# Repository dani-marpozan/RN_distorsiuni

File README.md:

# Efectul reactiei negatie asupra distorsiunilor si  semnalelor parazite  

Model 3D

## Schematic

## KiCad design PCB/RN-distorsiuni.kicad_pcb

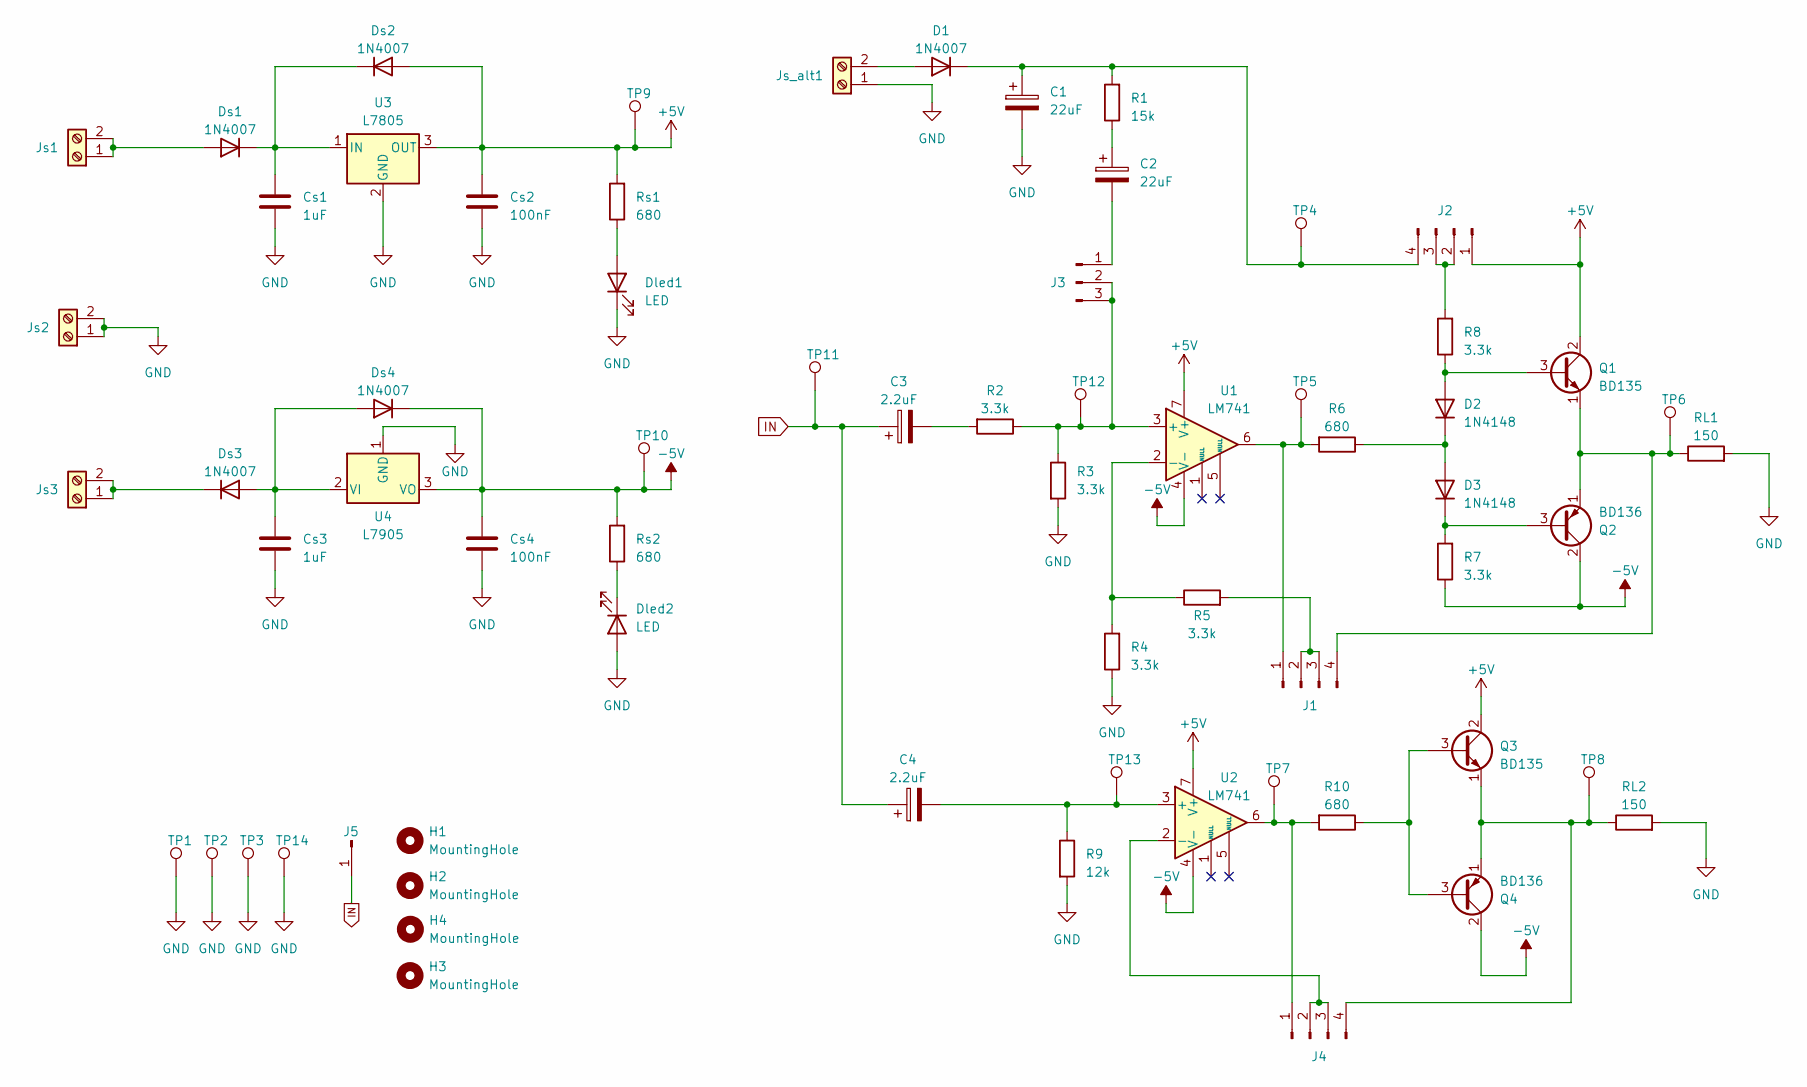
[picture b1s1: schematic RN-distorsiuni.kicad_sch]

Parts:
C1: 22uF; CP_Radial_D6.3mm_P2.50mm
C2: 22uF; C_Radial_D5.0mm_H11.0mm_P2.00mm
C3, C4: 2.2uF; C_Radial_D5.0mm_H11.0mm_P2.00mm
Cs1, Cs3: 1uF; C_Radial_D5.0mm_H11.0mm_P2.00mm
Cs2, Cs4: 100nF; C_Disc_D6.0mm_W2.5mm_P5.00mm
D1: 1N4007; D_DO-41_SOD81_P10.16mm_Horizontal
D2, D3: 1N4148; D_DO-35_SOD27_P7.62mm_Horizontal
Dled1, Dled2: LED; LED_D5.0mm
Ds1, Ds2, Ds3, Ds4: 1N4007; D_DO-41_SOD81_P10.16mm_Horizontal
H1, H2, H3, H4: MountingHole; MountingHole_3.2mm_M3_ISO7380_Pad_TopBottom
J1, J2, J4: Conn_01x04_Pin; PinHeader_1x04_P2.54mm_Vertical
J3: Conn_01x03_Pin; PinHeader_1x03_P2.54mm_Vertical
J5: Conn_01x01_Male; TestPoint
Js1, Js2, Js3: Screw_Terminal_01x02; TerminalBlock_Phoenix_MKDS-1,5-2_1x02_P5.00mm_Horizontal
Js_alt1: Screw_Terminal_01x02; TerminalBlock_Phoenix_MKDS-1,5-2_1x02_P5.00mm_Horizontal
Q1, Q3: BD135; TO-126-3_Vertical
Q2, Q4: BD136; TO-126-3_Vertical
R1: 15k; R_Axial_DIN0207_L6.3mm_D2.5mm_P10.16mm_Horizontal
R2, R3, R4, R5, R7, R8: 3.3k; R_Axial_DIN0207_L6.3mm_D2.5mm_P10.16mm_Horizontal
R6, R10: 680; R_Axial_DIN0207_L6.3mm_D2.5mm_P10.16mm_Horizontal
R9: 12k; R_Axial_DIN0207_L6.3mm_D2.5mm_P10.16mm_Horizontal
RL1, RL2: 150; R_Axial_DIN0207_L6.3mm_D2.5mm_P10.16mm_Horizontal
Rs1, Rs2: 680; R_Axial_DIN0207_L6.3mm_D2.5mm_P10.16mm_Horizontal
TP1, TP2, TP3, TP14: TestPoint
TP4, TP5, TP6, TP7, TP8, TP9, TP10, TP11, TP12, TP13: TestPoint; Kesytone TP Multipurpose 5013
U1, U2: LM741; DIP-8_W7.62mm
U3: L7805; TO-220-3_Vertical
U4: L7905; TO-220-3_Vertical

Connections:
+5V: Cs2.1, Ds2.2 (A), J2.1, Q1.2 (C), Q3.2 (C), Rs1.2, TP9.1, U1.7 (V+), U2.7 (V+), U3.3 (OUT)
-5V: Cs4.1, Ds4.1 (K), Q2.2 (C), Q4.2 (C), R7.1, Rs2.2, TP10.1, U1.4 (V-), U2.4 (V-), U4.3 (VO)
GND: C1.2, Cs1.2, Cs2.2, Cs3.2, Cs4.2, Dled1.1 (K), Dled2.2 (A), Js2.1, Js2.2, Js_alt1.1, R3.2, R4.1, R9.2, RL1.2, RL2.2, TP1.1, TP2.1, TP3.1, TP14.1, U3.2 (GND), U4.1 (GND)
IN: C3.1, C4.1, J5.1, TP11.1
unnamed: C2.1, R1.1
unnamed: C3.2, R2.2
unnamed: D1.2 (A), Js_alt1.2
unnamed: C1.1, D1.1 (K), J2.4, R1.2, TP4.1
unnamed: D2.2 (A), Q1.3 (B), R8.1
unnamed: D2.1 (K), D3.2 (A), R6.1
unnamed: D3.1 (K), Q2.3 (B), R7.2
unnamed: Dled1.2 (A), Rs1.1
unnamed: Dled2.1 (K), Rs2.1
unnamed: Ds1.2 (A), Js1.1, Js1.2
unnamed: Cs1.1, Ds1.1 (K), Ds2.1 (K), U3.1 (IN)
unnamed: Cs3.1, Ds3.2 (A), Ds4.2 (A), U4.2 (VI)
unnamed: Ds3.1 (K), Js3.1, Js3.2
unnamed: J1.1, R6.2, TP5.1, U1.6
unnamed: J1.2, J1.3, R5.2
unnamed: J1.4, Q1.1 (E), Q2.1 (E), RL1.1, TP6.1
unnamed: J2.2, J2.3, R8.2
unnamed: C2.2, J3.1
unnamed: J3.2, J3.3, R2.1, R3.1, TP12.1, U1.3 (+)
unnamed: J4.1, R10.2, TP7.1, U2.6
unnamed: J4.2, J4.3, U2.2 (-)
unnamed: J4.4, Q3.1 (E), Q4.1 (E), RL2.1, TP8.1
unnamed: Q3.3 (B), Q4.3 (B), R10.1
unnamed: R4.2, R5.1, U1.2 (-)
unnamed: C4.2, R9.1, TP13.1, U2.3 (+)

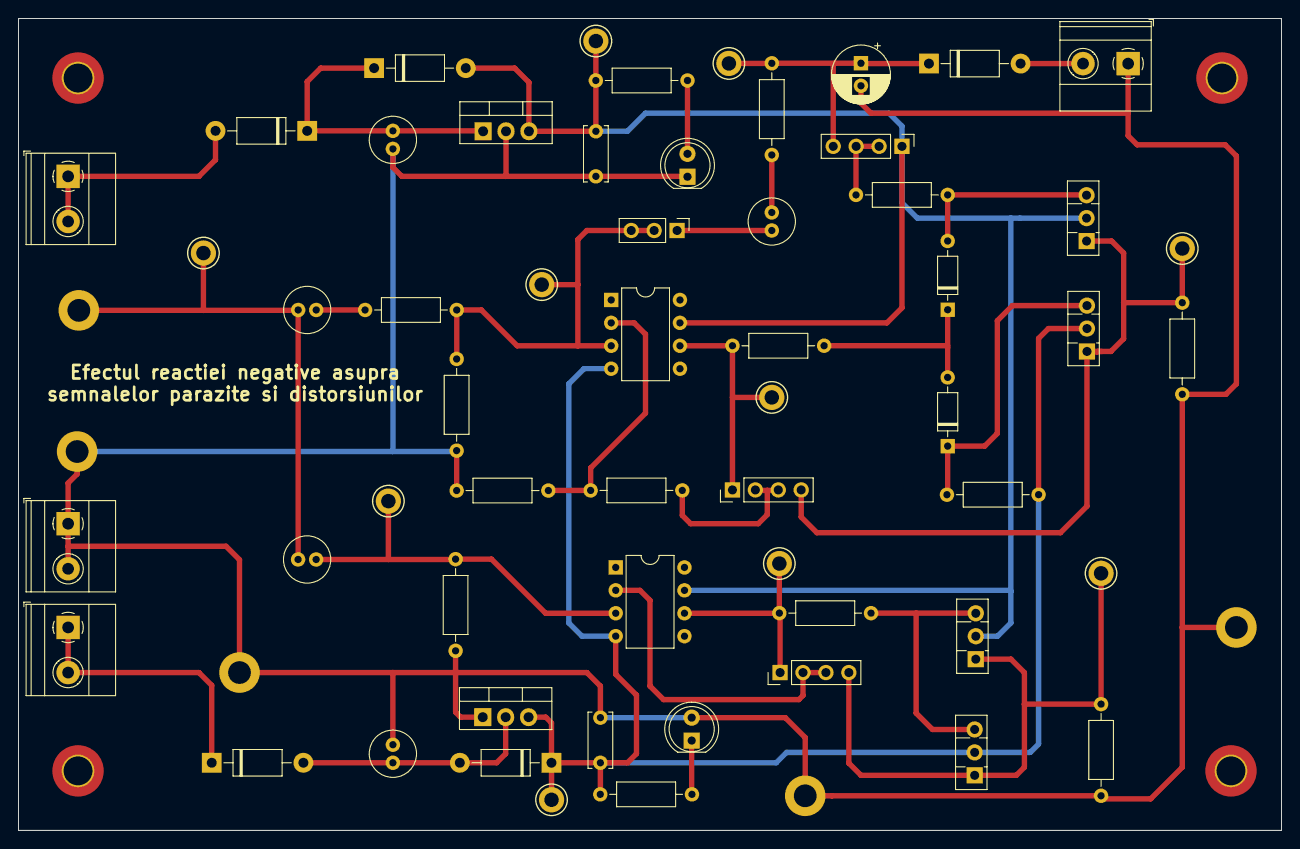
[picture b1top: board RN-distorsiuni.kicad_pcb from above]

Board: 2 copper layers, 140.0 x 90.0 mm, 66 parts (0 on the bottom side), 29 nets.
